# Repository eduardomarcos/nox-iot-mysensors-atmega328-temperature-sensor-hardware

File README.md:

# Arduino Atmega 328 RF Temperature and Humidity Sensor 

## Custom temperature and humidity sensor using an atmega 328 PU as CPU and NRF24L01 as radio to send data over RF using MySensors framework.

_Currently working to make the PCB valid for this enclosure:_

https://es.aliexpress.com/item/32901643453.html

The hardware is the following:

And this is the current PCB:

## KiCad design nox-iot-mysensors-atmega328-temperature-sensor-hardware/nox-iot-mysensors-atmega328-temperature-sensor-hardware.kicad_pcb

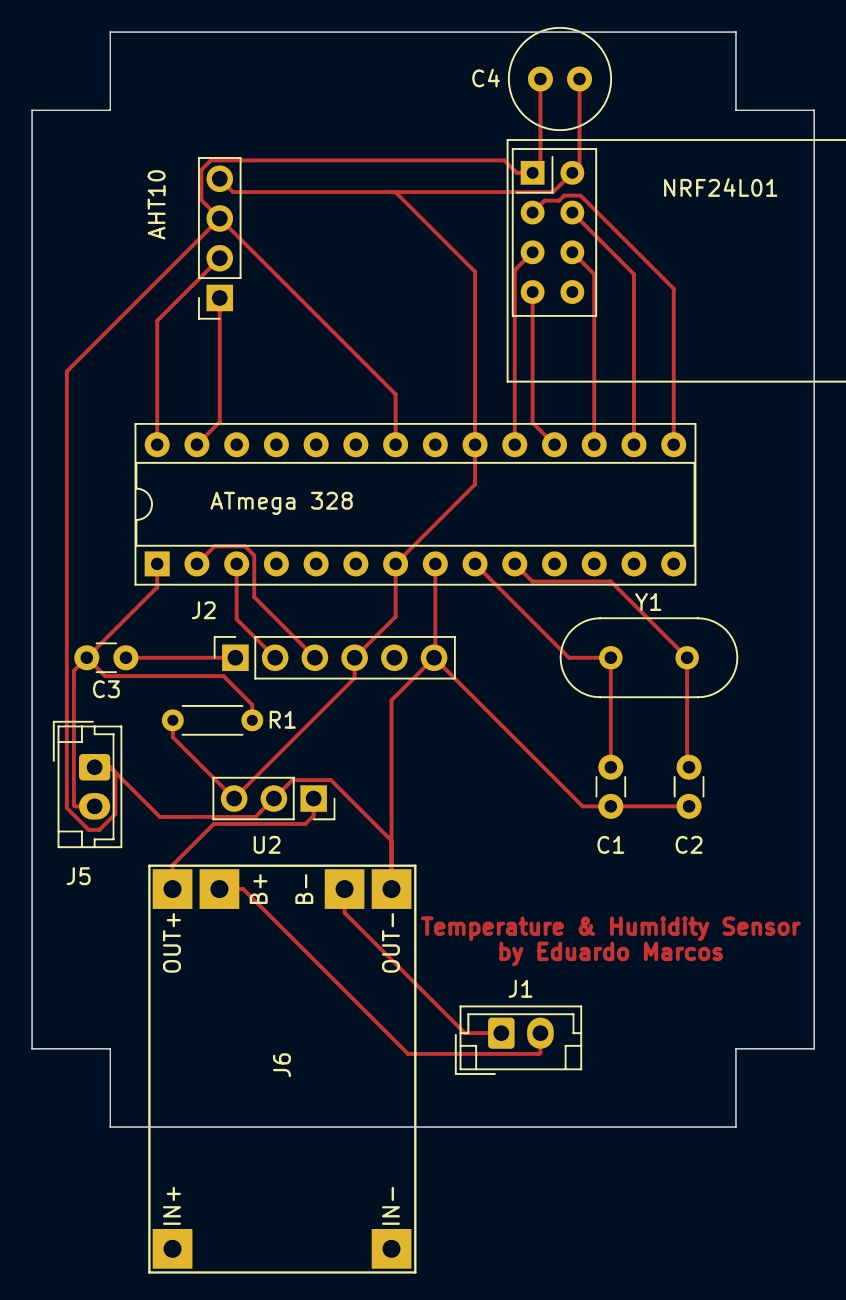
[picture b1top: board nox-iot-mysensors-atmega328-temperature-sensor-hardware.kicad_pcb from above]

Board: 2 copper layers, 50.0 x 70.0 mm, 14 parts (0 on the bottom side), 18 nets.

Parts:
AHT10: AHT10; PinSocket_1x04_P2.54mm_Vertical
ATmega 328: ATmega328P-PU; DIP-28_W7.62mm_Socket
C1, C2: 22uF; C_Disc_D3.0mm_W1.6mm_P2.50mm
C3: 104uF; C_Disc_D3.0mm_W1.6mm_P2.50mm
C4: 10uF; C_Radial_D6.3mm_H5.0mm_P2.50mm
J1: Vin; JST_EH_B2B-EH-A_1x02_P2.50mm_Vertical
J2: FTDI232; PinSocket_1x06_P2.54mm_Vertical
J5: Switch Connector; JST_EH_B2B-EH-A_1x02_P2.50mm_Vertical
J6: TP4056
NRF24L01: NRF24L01+; nRF24L01_Breakout
R1: 10K; R_Axial_DIN0204_L3.6mm_D1.6mm_P5.08mm_Horizontal
U2: WAVGAT 3.3V; PinSocket_1x03_P2.54mm_Vertical
Y1: 16 MHZ; Crystal_HC49-U_Vertical

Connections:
3.3V: AHT10.4, ATmega 328.7, ATmega 328.20, C4.1, J2.4, NRF24L01.2, R1.1, U2.3
+4V: J6.3, U2.1
+BATT: J1.2, J6.5
-BATT: J1.1, J6.6
/DTR: C3.1, J2.1
/RX: ATmega 328.3, J2.2
/SCL: AHT10.2, ATmega 328.28
/SDA: AHT10.1, ATmega 328.27
/TX: ATmega 328.2, J2.3
GND: AHT10.3, ATmega 328.8, ATmega 328.22, C1.1, C2.1, C4.2, J2.6, J5.1, J6.4, NRF24L01.1, U2.2
unnamed: ATmega 328.9, C1.2, Y1.1
unnamed: ATmega 328.10, C2.2, Y1.2
unnamed: ATmega 328.1, C3.2, J5.2, R1.2
unnamed: ATmega 328.15, NRF24L01.3
unnamed: ATmega 328.16, NRF24L01.4
unnamed: ATmega 328.17, NRF24L01.6
unnamed: ATmega 328.18, NRF24L01.7
unnamed: ATmega 328.19, NRF24L01.5

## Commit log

2020-03-21 pcb first attemp
2020-03-21 temperature sensor schema
2020-03-21 wires complete for perfboard
2020-03-21 aht10 sensor instead of dht11 and 3.3v boost
2020-03-21 components in place
    before wiring components por perfboard
2020-03-21 adjust to 10uF the NRF24L01 capacitor
2020-03-21 change switch button to switch connector
2020-03-21 Create Readme file
2020-03-22 upload schematics and pcb images
2020-03-22 update readme with images
2020-03-23 updated with proper pcb
2020-03-23 ignore gerber files
